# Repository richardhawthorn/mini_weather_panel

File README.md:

### Description

Weather screen used to display current and upcoming weather conditions

- Current temperature
- Todays max temperature
- Todays weather icon (sun, cloud etc)
- Rainfall for the next 24 hours

#### Instructions

Config information is stored on the micro SD card, inserted into the back of the board.
Copy the example config.txt file (found in the code folder) onto a blank sd card, and add the relevant config information.

Sign up for a free api key at https://openweathermap.org/api and add that to the config file

This config file is used to set the following:

- Network details
- Open weather map API key
- Location (for weather reporting)
- Units
- Timezone

#### Arduino config

You will need to use the ESP8266 Arduino core to compile and upload this code
https://github.com/esp8266/Arduino

These libraries are also required

- Time - http://www.pjrc.com/teensy/td_libs_Time.html
- Adafruit LED Backpack - https://github.com/adafruit/Adafruit_LED_Backpack
- Adafurit GFX - https://github.com/adafruit/Adafruit-GFX-Library

#### Hardware

- ESP8266 Wifi processor
- 2 x 7 segment LED screens
- 2 x 8x8 matrix LED screens 
- FTDI headers for programming
- Mini USB for power

### License

This work is licensed under a Creative Commons Attribution-ShareAlike 4.0 International License.

<br />
Designed by <a xmlns:cc="http://creativecommons.org/ns#" href="http://www.richardhawthorn.com" property="cc:attributionName" rel="cc:attributionURL" target="_blank">Richard Hawthorn</a><br />
<a rel="license" href="http://creativecommons.org/licenses/by-sa/4.0/" target="_blank">View License</a>

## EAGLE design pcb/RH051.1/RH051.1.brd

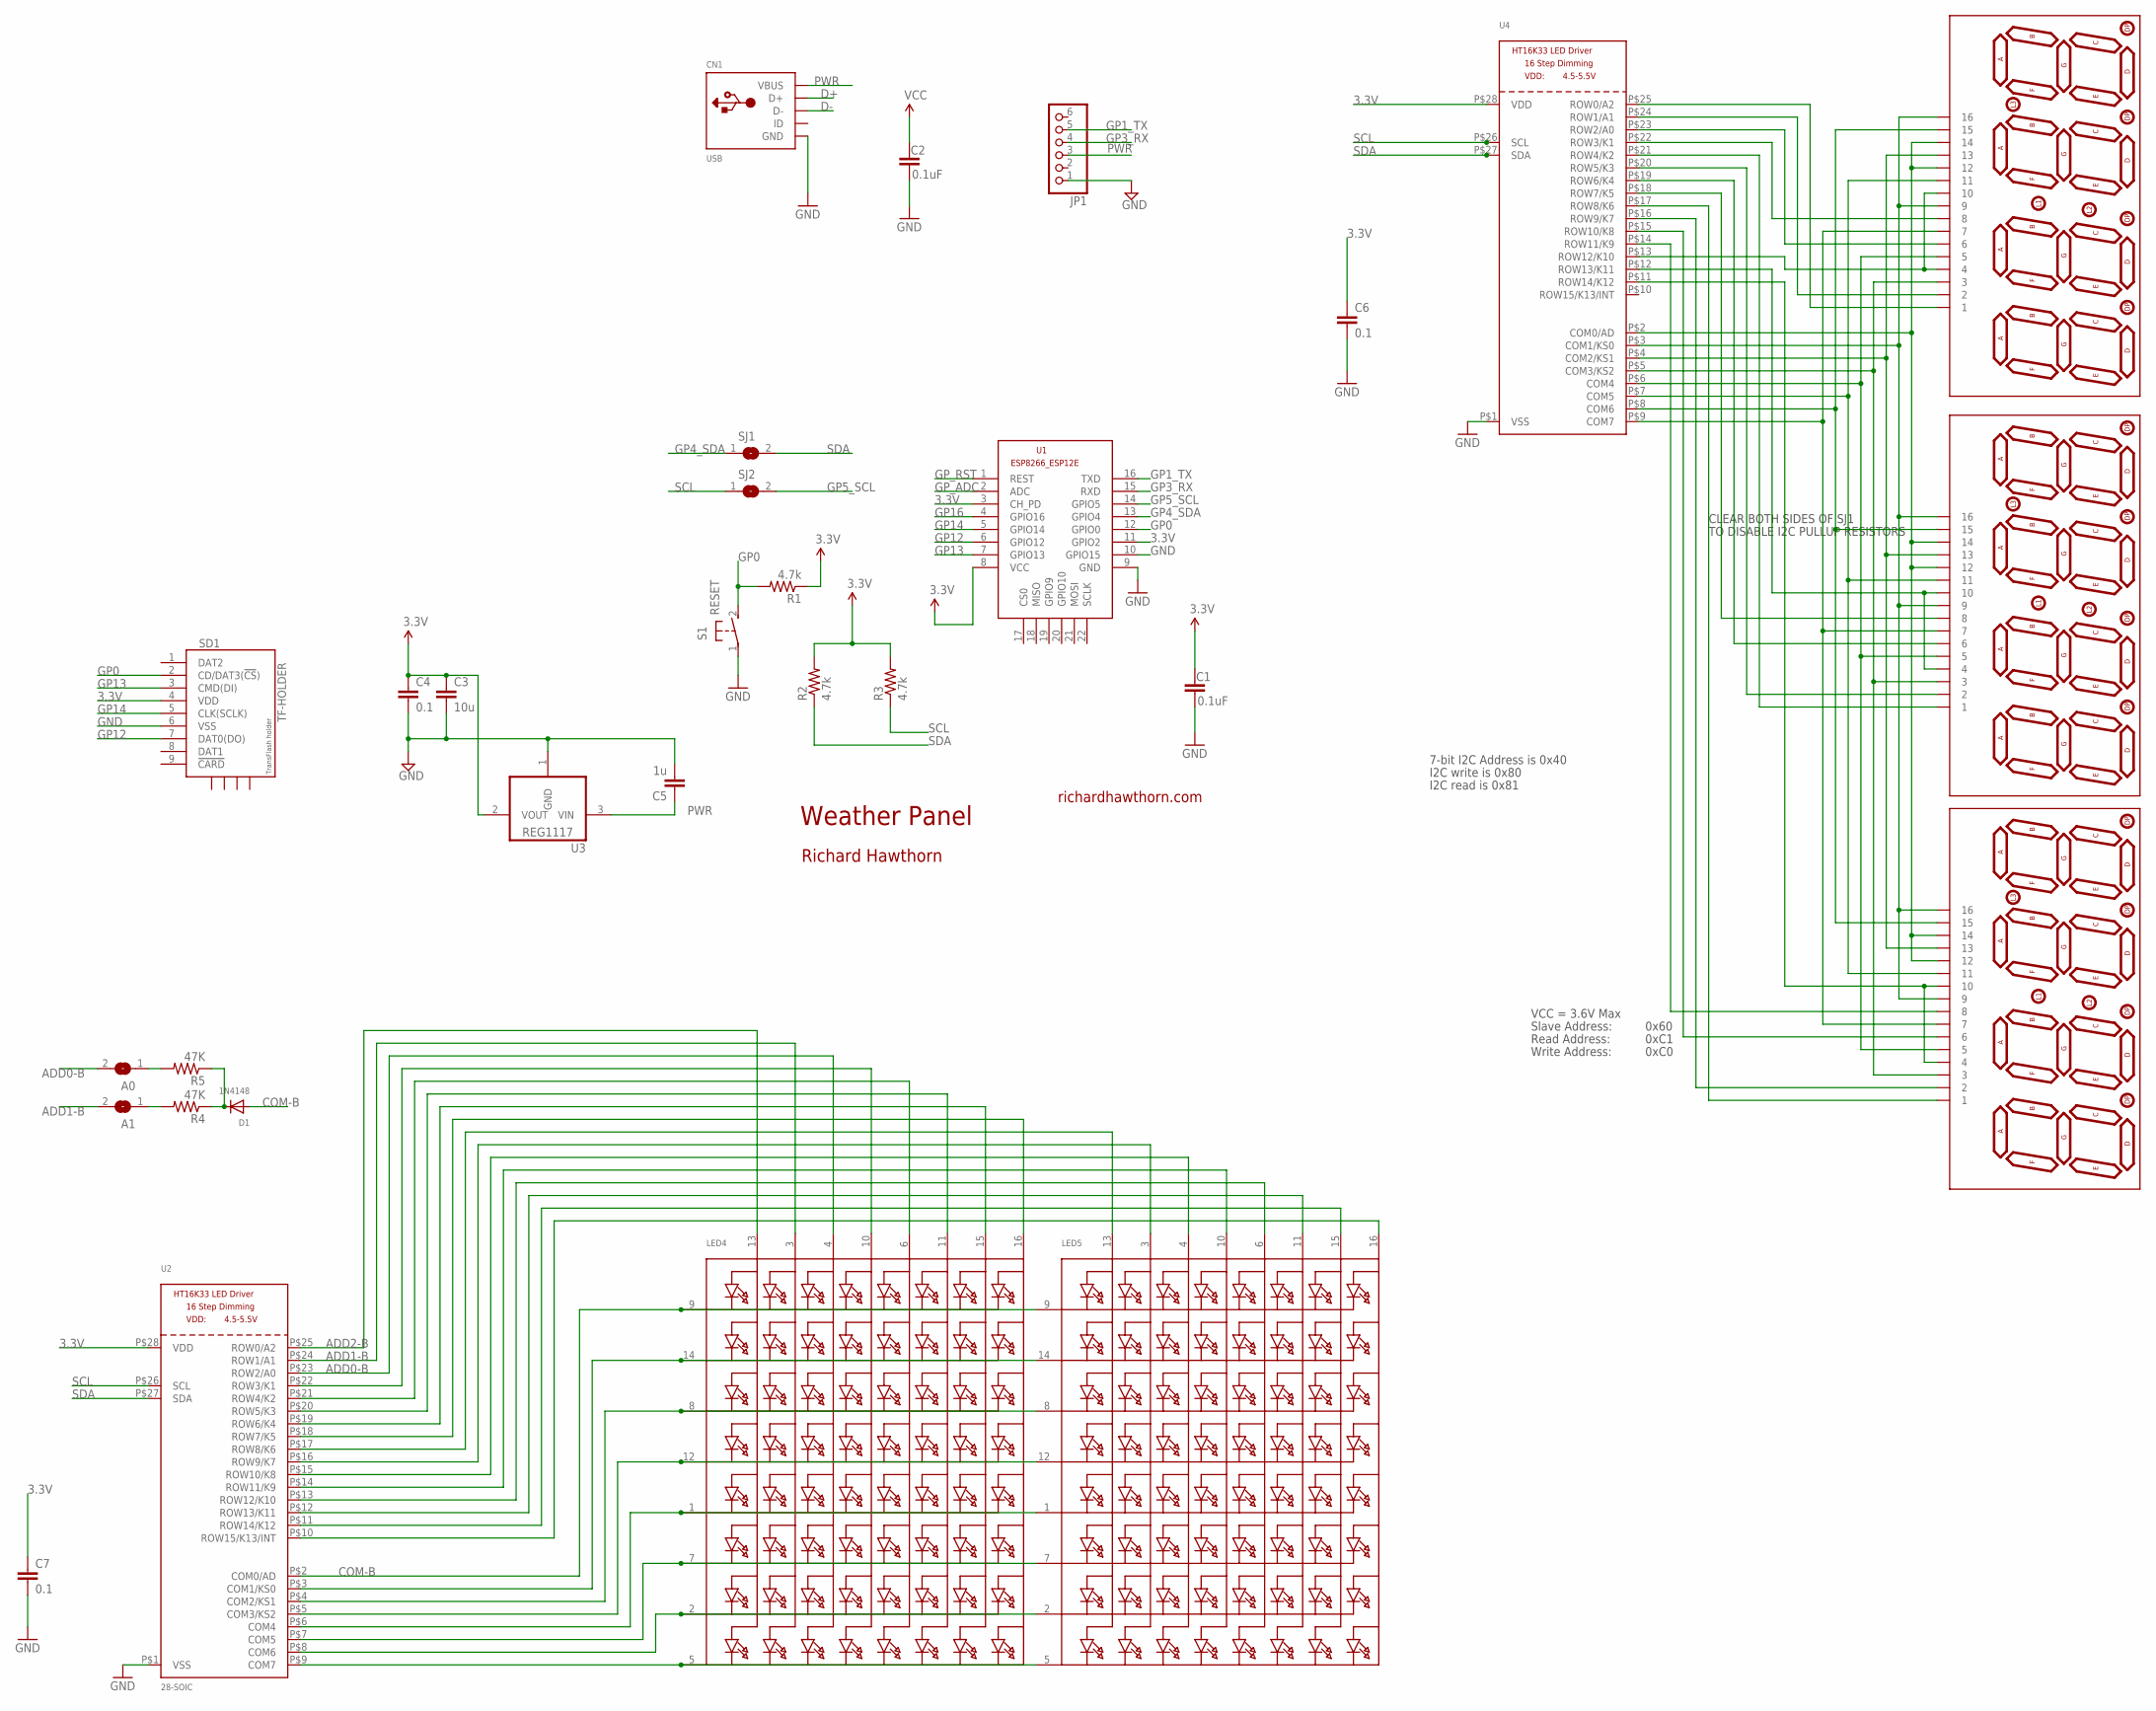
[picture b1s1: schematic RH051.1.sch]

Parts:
A0, A1: SOLDERJUMPERREFLOW_NOPASTE; SOLDERJUMPER_REFLOW_NOPASTE
C1, C2: 0.1uF; 0603-CAP
C3: 10u; 0805-CAP
C4, C6, C7: 0.1; 0603-CAP
C5: 1u; 0603-CAP
CN1: USB; USB-MINIB
D1: 1N4148; SOD-323F
JP1: PINHD-1X6; 1X06
LED1, LED2, LED3: 7SEG-4DIGIT; SPARKFUN_7-SEGMENT-4DIGIT
LED4, LED5: DISP_SEGMENT_8X8_ROWCATHODEM12A881UR; SEGMENT_BL-M12A881UR
R1, R2, R3: 4.7k; 0805
R4, R5: 47K; R0805
S1: RESET; DTSM-3
SD1: TF-HOLDER; TF-PULL
SJ1, SJ2: SJ
U1: ESP8266-12EESP8266-ESP12E; ESP8266-ESP12E
U2: 28-SOIC; SOP28_300MIL
U3: REG1117; SOT223
U4: HT16K33_SOP28; SOP28_300MIL

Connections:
3.3V: C1.1, C2.1, C3.1, C4.1, C6.1, C7.1, R1.1, R2.2, R3.2, SD1.4 (VDD), U1.3 (CH_PD), U1.8 (VCC), U1.11 (GPIO2), U2.P$28 (VDD), U3.2 (VOUT), U4.P$28 (VDD)
ADD0-A: LED1.6, U4.P$23 (ROW2/A0)
ADD0-B: A0.2, LED4.4 (A3), U2.P$23 (ROW2/A0)
ADD1-A: LED1.2, U4.P$24 (ROW1/A1)
ADD1-B: A1.2, LED4.3 (A2), U2.P$24 (ROW1/A1)
ADD2-A: LED1.1, U4.P$25 (ROW0/A2)
ADD2-B: LED4.13 (A1), U2.P$25 (ROW0/A2)
COM-A: LED1.12, LED1.14, LED2.12, LED2.14, LED3.12, LED3.14, U4.P$2 (COM0/AD)
COM-B: D1.A, LED4.9 (K1), LED5.9 (K1), U2.P$2 (COM0/AD)
D+: CN1.D+
D-: CN1.D-
GND: C1.2, C2.2, C3.2, C4.2, C5.2, C6.2, C7.2, CN1.GND, JP1.1, S1.1, SD1.6 (VSS), U1.9 (GND), U1.10 (GPIO15), U2.P$1 (VSS), U3.1 (GND), U4.P$1 (VSS)
GP0: R1.2, S1.2, SD1.2 (CD/DAT3(!CS!)), U1.12 (GPIO0)
GP1_TX: JP1.5, U1.16 (TXD)
GP3_RX: JP1.4, U1.15 (RXD)
GP4_SDA: SJ1.1, U1.13 (GPIO4)
GP5_SCL: SJ2.2, U1.14 (GPIO5)
GP12: SD1.7 (DAT0(DO)), U1.6 (GPIO12)
GP13: SD1.3 (CMD(DI)), U1.7 (GPIO13)
GP14: SD1.5 (CLK(SCLK)), U1.5 (GPIO14)
GP16: U1.4 (GPIO16)
GP_ADC: U1.2 (ADC)
GP_RST: U1.1 (REST)
unnamed: LED4.5 (K8), LED5.5 (K8), U2.P$9 (COM7)
unnamed: LED4.2 (K7), LED5.2 (K7), U2.P$8 (COM6)
unnamed: LED4.7 (K6), LED5.7 (K6), U2.P$7 (COM5)
unnamed: LED1.9, LED1.16, LED2.9, LED2.16, LED3.9, LED3.16, U4.P$3 (COM1/KS0)
unnamed: LED1.13, LED2.13, LED3.13, U4.P$4 (COM2/KS1)
unnamed: LED1.3, LED2.3, LED3.3, U4.P$5 (COM3/KS2)
unnamed: LED1.5, LED2.5, LED3.5, U4.P$6 (COM4)
unnamed: LED1.11, LED2.11, LED3.11, U4.P$7 (COM5)
unnamed: LED1.15, LED2.15, LED3.15, U4.P$8 (COM6)
unnamed: LED1.7, LED2.7, LED3.7, U4.P$9 (COM7)
unnamed: LED4.1 (K5), LED5.1 (K5), U2.P$6 (COM4)
unnamed: LED4.8 (K3), LED5.8 (K3), U2.P$4 (COM2/KS1)
unnamed: LED4.14 (K2), LED5.14 (K2), U2.P$3 (COM1/KS0)
unnamed: LED1.8, U4.P$22 (ROW3/K1)
unnamed: LED2.1, U4.P$21 (ROW4/K2)
unnamed: LED2.2, U4.P$20 (ROW5/K3)
unnamed: LED2.6, U4.P$19 (ROW6/K4)
unnamed: LED2.8, U4.P$18 (ROW7/K5)
unnamed: LED3.1, U4.P$17 (ROW8/K6)
unnamed: LED3.2, U4.P$16 (ROW9/K7)
unnamed: LED3.6, U4.P$15 (ROW10/K8)
unnamed: LED3.8, U4.P$14 (ROW11/K9)
unnamed: LED1.4, LED1.10, U4.P$13 (ROW12/K10)
unnamed: LED2.4, LED2.10, U4.P$12 (ROW13/K11)
unnamed: LED3.4, LED3.10, U4.P$11 (ROW14/K12)
unnamed: LED5.15 (A7), U2.P$11 (ROW14/K12)
unnamed: LED5.11 (A6), U2.P$12 (ROW13/K11)
unnamed: LED4.16 (A8), U2.P$18 (ROW7/K5)
unnamed: LED4.15 (A7), U2.P$19 (ROW6/K4)
unnamed: LED4.6 (A5), U2.P$21 (ROW4/K2)
unnamed: LED4.10 (A4), U2.P$22 (ROW3/K1)
unnamed: LED5.16 (A8), U2.P$10 (ROW15/K13/INT)
unnamed: LED4.11 (A6), U2.P$20 (ROW5/K3)
unnamed: LED4.12 (K4), LED5.12 (K4), U2.P$5 (COM3/KS2)
unnamed: A1.1, R4.2
unnamed: LED5.13 (A1), U2.P$17 (ROW8/K6)
unnamed: LED5.3 (A2), U2.P$16 (ROW9/K7)
unnamed: LED5.10 (A4), U2.P$14 (ROW11/K9)
unnamed: LED5.4 (A3), U2.P$15 (ROW10/K8)
unnamed: LED5.6 (A5), U2.P$13 (ROW12/K10)
unnamed: A0.1, R5.2
unnamed: D1.C, R4.1, R5.1
PWR: C5.1, CN1.VBUS, JP1.3, U3.3 (VIN)
SCL: R3.1, SJ2.1, U2.P$26 (SCL), U4.P$26 (SCL)
SDA: R2.1, SJ1.2, U2.P$27 (SDA), U4.P$27 (SDA)

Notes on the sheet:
Weather Panel
richardhawthorn.com
Richard Hawthorn
CLEAR BOTH SIDES OF SJ1
TO DISABLE I2C PULLUP RESISTORS
7-bit I2C Address is 0x40
I2C write is 0x80
I2C read is 0x81
VCC = 3.6V Max
Read Address:
Write Address:
Slave Address:
0x60
0xC1
0xC0

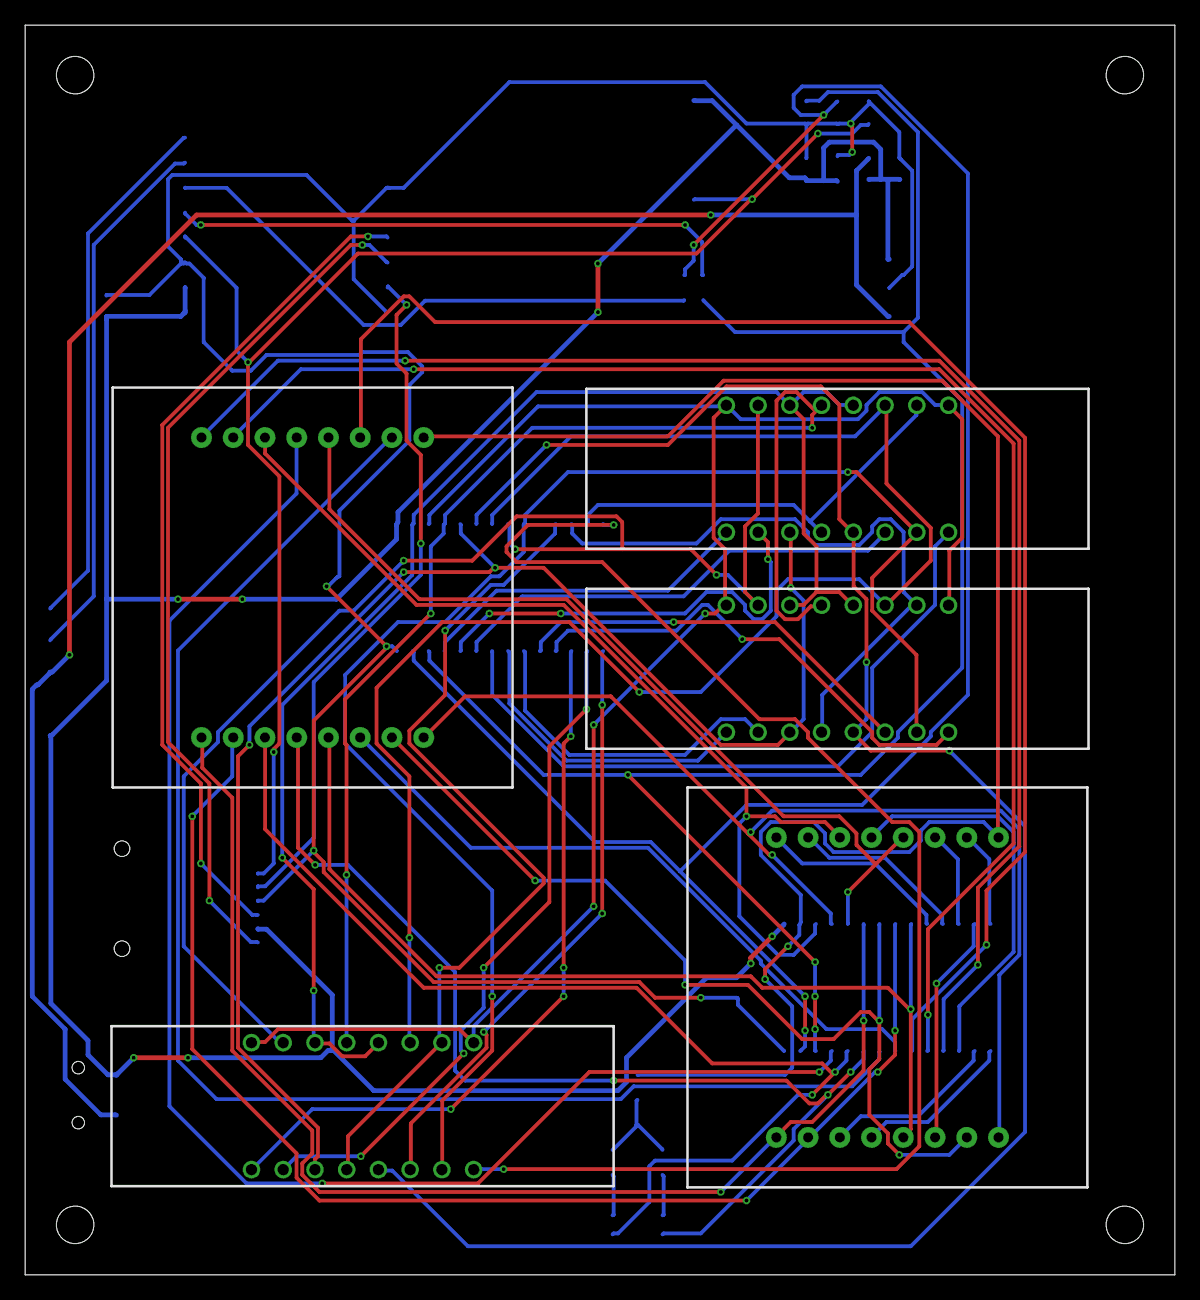
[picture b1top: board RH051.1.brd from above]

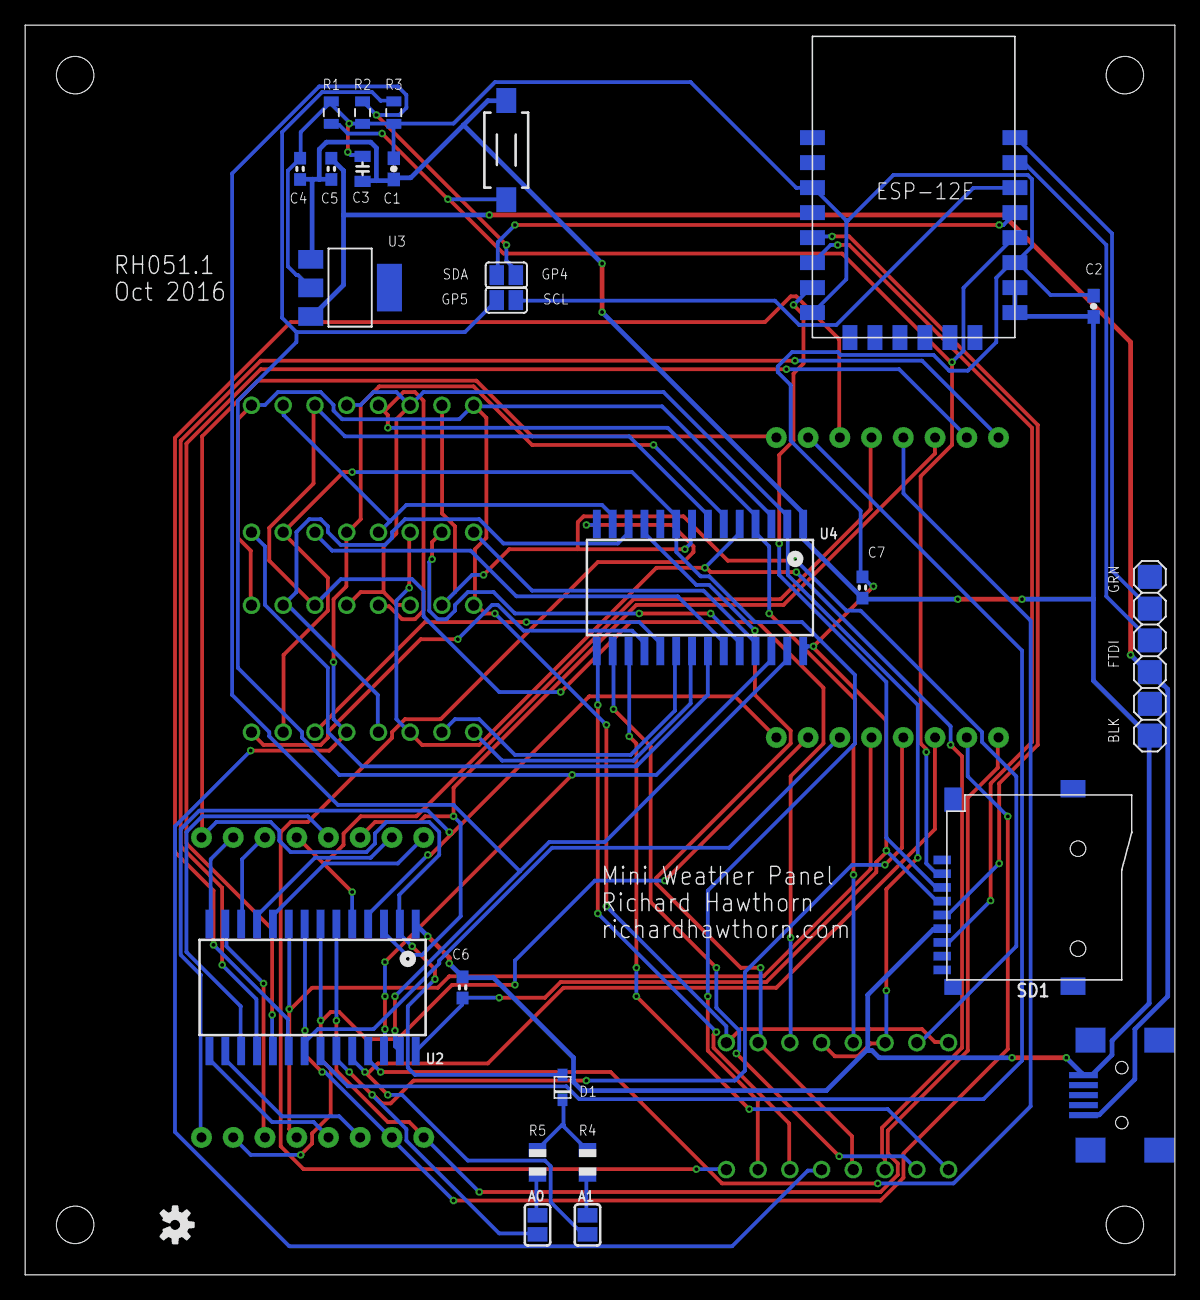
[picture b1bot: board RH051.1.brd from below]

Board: 2 copper layers, 92.0 x 100.0 mm, 31 parts (26 on the bottom side), 63 nets.

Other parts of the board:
U$3: OSHW-LOGO-S

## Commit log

2016-11-08 Add PCB and readme
2016-11-08 Adding front panel
2016-11-08 Adding Arduino code
2016-11-10 update Arduino code header
2017-01-20 new connection visual + config file reading
2017-01-24 add images
2017-01-24 add image

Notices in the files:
parts and their libraries:
SparkFun-Aesthetics: Licensing: CC v3.0 Share-Alike You are welcome to use this library for commercial purposes.
